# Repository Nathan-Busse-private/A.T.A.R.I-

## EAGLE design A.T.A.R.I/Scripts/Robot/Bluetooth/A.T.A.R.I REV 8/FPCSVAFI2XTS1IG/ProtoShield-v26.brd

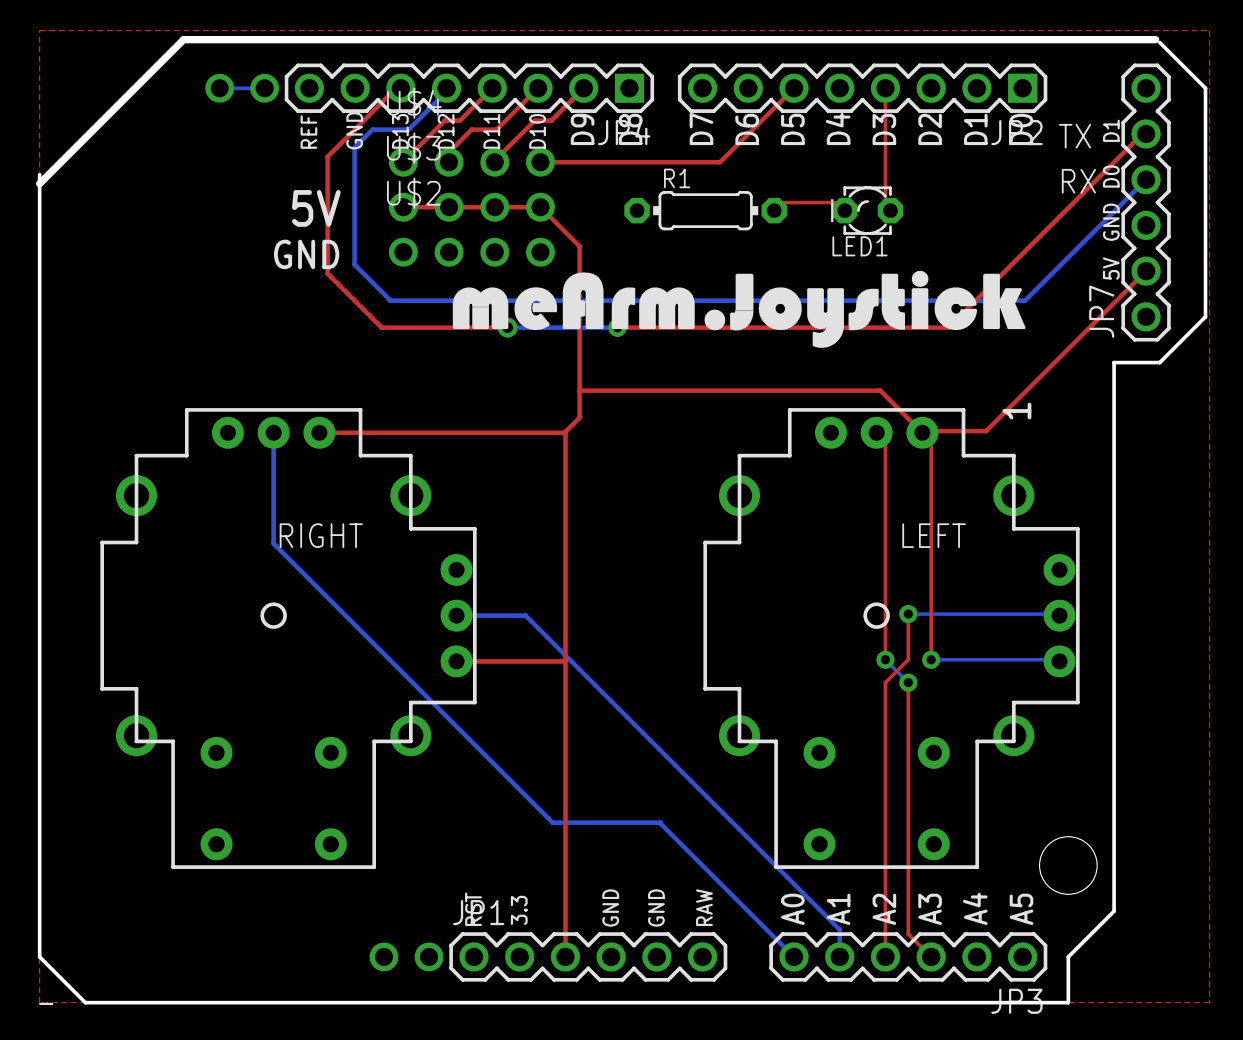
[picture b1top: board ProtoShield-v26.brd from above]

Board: 2 copper layers, 64.7 x 53.4 mm, 12 parts (0 on the bottom side), 14 nets.

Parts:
JP1: Power; 1X06
JP2: Digital1; 1X08
JP3: Analog; 1X06
JP4: Digital2; 1X08
JP7: BlueSMiRF; 1X06
LED1: LED_LD260
LEFT: JOYSTICKPTH; JOYSTICK
R1: 0204/7
RIGHT: JOYSTICKPTH; JOYSTICK
U$2, U$3, U$4: JUMP4

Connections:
A0: JP3.6, RIGHT.H2
A1: JP3.5, RIGHT.V2
A2: JP3.4, LEFT.V2
A3: JP3.3, LEFT.H2
D3: JP2.4, LED1.A
D5: JP2.6, U$4.2
D9: JP4.2, U$4.4
D10: JP4.3, U$4.6
D11: JP4.4, U$4.8
D12: JP4.5, JP7.4
D13: JP4.6, JP7.5
GND: JP1.4, JP1.5, JP4.7, JP7.3, LEFT.H3, LEFT.V3, R1.1, RIGHT.H3, RIGHT.V3, U$2.2, U$2.4, U$2.6, U$2.8
unnamed: LED1.K, R1.2
VCC: JP1.3, JP7.2, LEFT.H1, LEFT.V1, RIGHT.H1, RIGHT.V1, U$3.2, U$3.4, U$3.6, U$3.8

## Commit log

2023-12-19 Update
    Fixed a bug where motor B does not change speed when changing speed within the app.
2023-12-20 Update
    Bug fixes.
2023-12-25 Update
    Added headlights to the rover.
